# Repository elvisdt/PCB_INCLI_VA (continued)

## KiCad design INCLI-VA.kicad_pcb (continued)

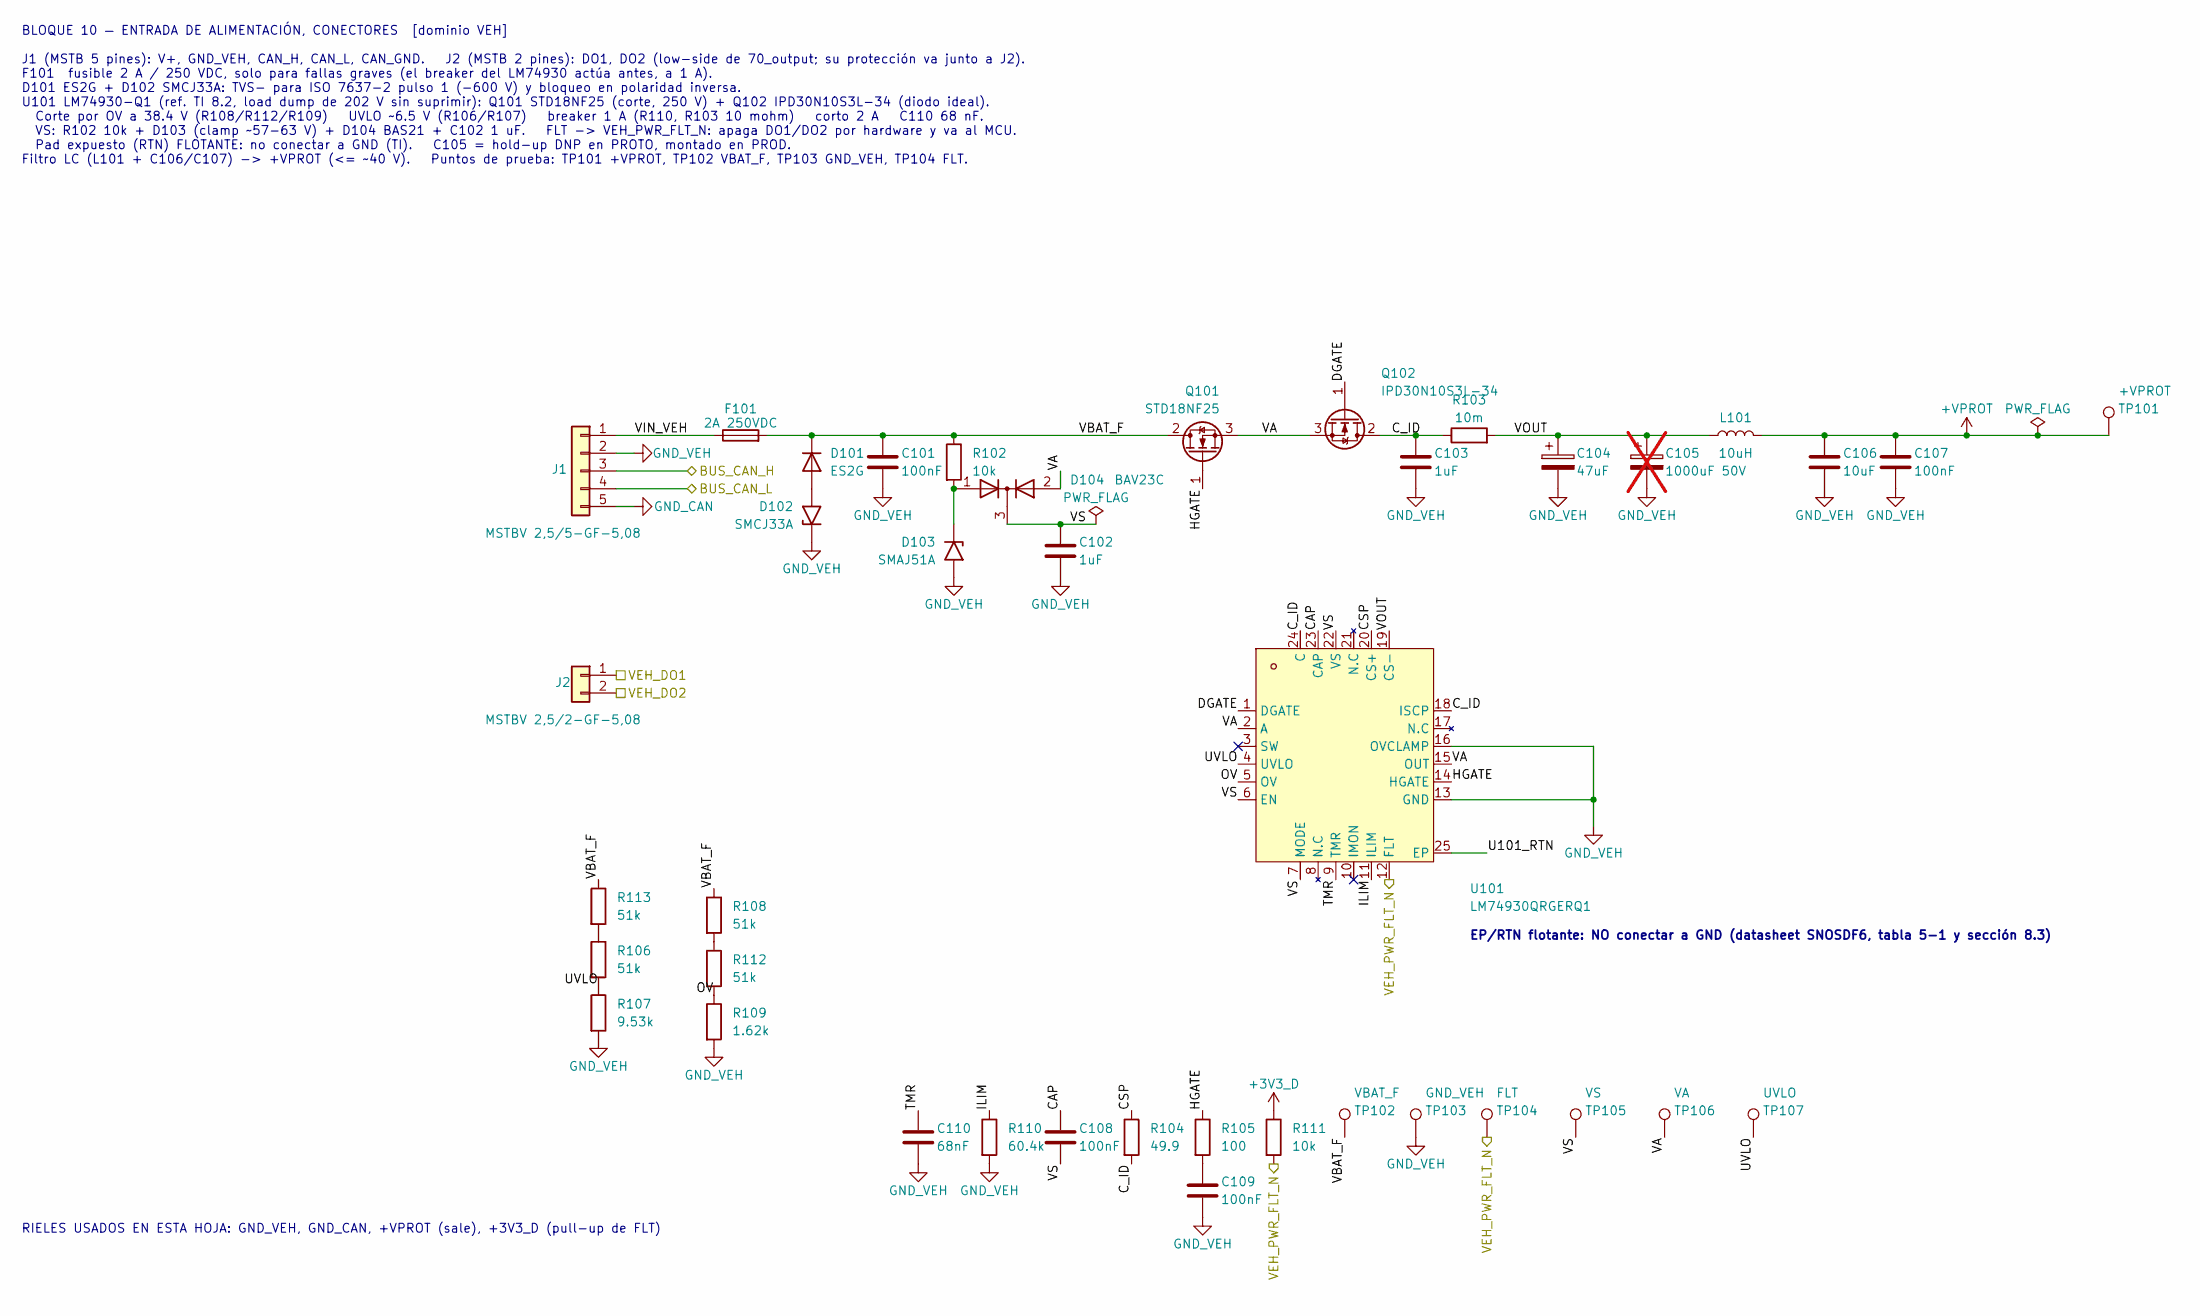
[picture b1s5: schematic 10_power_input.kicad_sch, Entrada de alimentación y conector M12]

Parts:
C101: 100nF; C_1206_3216Metric; MPN CGA5L4X7T2W104K160AA; LCSC C3887150
C102, C103: 1uF; C_1206_3216Metric; MPN CGA5L2X7R2A105K160AA; LCSC C2168321
C104: 47uF; CP_Elec_10x10; MPN EEE-HA2A470UP; LCSC C344077
C105: 1000uF 50V; CP_Elec_Panasonic_J16_VibProof; MPN EEE-FK1H102AV; LCSC C2164039; not fitted
C106: 10uF; C_1210_3225Metric; MPN GCM32ER71H106KA12L; LCSC_PROTO C138687
C107, C108, C109: 100nF; C_0603_1608Metric; MPN GCM188R72A104KA64D; LCSC C415406
C110: 68nF; C_0603_1608Metric; MPN GCM188R71H683KA57D; LCSC C380380
D101: ES2G; D_SMB; MPN ES2G-E3/52T; LCSC C2927419
D102: SMCJ33A; D_SMC; MPN SMCJ33A; LCSC C438109
D103: SMAJ51A; D_SMA; MPN SMAJ51A; LCSC C366557
D104: BAV23C; SOT-23; MPN BAV23C,215; LCSC C282370
F101: 2A 250VDC; Fuse_Bourns_SF-2410; MPN SF-2410FPA200W-2; LCSC C3159902
J1: MSTBV 2,5/5-GF-5,08; PhoenixContact_MSTBV_2,5_5-GF-5,08_1x05_P5.08mm_Vertical_Th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; MPN 1777109; LCSC C7164734
J2: MSTBV 2,5/2-GF-5,08; PhoenixContact_MSTBV_2,5_2-GF-5,08_1x02_P5.08mm_Vertical_Th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; MPN 1777073; LCSC C480552
L101: 10uH; L_Bourns_SRN6045TA; MPN SRN6045TA-100M; LCSC C2046332
Q101: STD18NF25; TO-252-2; MPN STD18NF25; LCSC C183634
Q102: IPD30N10S3L-34; TO-252-2; MPN IPD30N10S3L34ATMA1; LCSC C148263
R102: 10k; R_2512_6332Metric; MPN AC2512FK-0710KL; LCSC C469651
R103: 10m; R_1206_3216Metric; MPN ERJ-8BWFR010V; LCSC C2076185
R104: 49.9; R_0603_1608Metric; MPN AC0603FR-0749R9L; LCSC C144653
R105: 100; R_0603_1608Metric; MPN AC0603FR-07100RL; LCSC C125923
R106, R108, R112, R113: 51k; R_1206_3216Metric; MPN AC1206FR-0751KL; LCSC C144484
R107: 9.53k; R_0603_1608Metric; MPN AC0603FR-079K53L; LCSC C228113
R109: 1.62k; R_0603_1608Metric; MPN AC0603FR-071K62L; LCSC C227657
R110: 60.4k; R_0603_1608Metric; MPN AC0603FR-0760K4L; LCSC C227994
R111: 10k; R_0603_1608Metric; MPN AC0603FR-0710KL; LCSC C116677
TP101: +VPROT; TestPoint_Pad_D1.5mm
TP102: VBAT_F; TestPoint_Pad_D1.5mm
TP103: GND_VEH; TestPoint_Pad_D1.5mm
TP104: FLT; TestPoint_Pad_D1.5mm
TP105: VS; TestPoint_Pad_D1.5mm
TP106: VA; TestPoint_Pad_D1.5mm
TP107: UVLO; TestPoint_Pad_D1.5mm
U101: LM74930QRGERQ1; TI_RGE0024T_VQFN-24-1EP_4x4mm_P0.5mm_EP2.1mm_HandSolder_Iso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; MPN LM74930QRGERQ1; LCSC C22428070

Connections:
+3V3_D: R111.1; also elsewhere on the board
+VPROT: C106.1, C107.1, L101.2, TP101.1 (1_1); also elsewhere on the board
/10_power_input/CAP: C108.1, U101.23 (CAP)
/10_power_input/CSP: R104.1, U101.20 (CS+)
/10_power_input/C_ID: C103.1, Q102.2 (D), R103.1, R104.2, U101.18 (ISCP), U101.24 (C)
/10_power_input/DGATE: Q102.1 (G), U101.1 (DGATE)
/10_power_input/HGATE: Q101.1 (G), R105.1, U101.14 (HGATE)
/10_power_input/ILIM: R110.1, U101.11 (ILIM)
/10_power_input/OV: R109.1, R112.2, U101.5 (OV)
/10_power_input/TMR: C110.1, U101.9 (TMR)
/10_power_input/U101_RTN: U101.25 (EP)
/10_power_input/UVLO: R106.2, R107.1, TP107.1, U101.4 (UVLO)
/10_power_input/VA: D104.2 (NC), Q101.3 (S), Q102.3 (S), TP106.1, U101.2 (A), U101.15 (OUT)
/10_power_input/VBAT_F: C101.1, D101.1 (K), F101.2, Q101.2 (D), R102.1, R108.1, R113.1, TP102.1 (1_1)
/10_power_input/VIN_VEH: F101.1, J1.1
/10_power_input/VOUT: C104.1, C105.1, L101.1, R103.2, U101.19 (CS-)
/10_power_input/VS: C102.1, C108.2, D104.3 (K), TP105.1, U101.6 (EN), U101.7 (MODE), U101.22 (VS)
/BUS_CAN_H: J1.3; also elsewhere on the board
/BUS_CAN_L: J1.4; also elsewhere on the board
/PWR_FLT_N: R111.2, TP104.1 (1_1), U101.12 (FLT); also elsewhere on the board
/VEH_DO1: J2.1; also elsewhere on the board
/VEH_DO2: J2.2; also elsewhere on the board
GND_CAN: J1.5; also elsewhere on the board
GND_VEH: C101.2, C102.2, C103.2, C104.2, C105.2, C106.2, C107.2, C109.2, C110.2, D102.1 (A1), D103.2 (A2), J1.2, R107.2, R109.2, R110.2, TP103.1 (1_1), U101.13 (GND), U101.16 (OVCLAMP); also elsewhere on the board
unnamed: C109.1, R105.2
unnamed: D101.2 (A), D102.2 (A2)
unnamed: D103.1 (A1), D104.1 (A), R102.2
unnamed: R106.1, R113.2
unnamed: R108.2, R112.1

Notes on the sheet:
BLOQUE 10 — ENTRADA DE ALIMENTACIÓN, CONECTORES [dominio VEH] J1 (MSTB 5 pines): V+, GND_VEH, CAN_H, CAN_L, CAN_GND. J2 (MSTB 2 pines): DO1, DO2 (low-side de 70_output; su protección va junto a J2). F101 fusible 2 A / 250 VDC, solo para fallas graves (el breaker del LM74930 actúa antes, a 1 A). D10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
EP/RTN flotante: NO conectar a GND (datasheet SNOSDF6, tabla 5-1 y sección 8.3)
RIELES USADOS EN ESTA HOJA: GND_VEH, GND_CAN, +VPROT (sale), +3V3_D (pull-up de FLT)

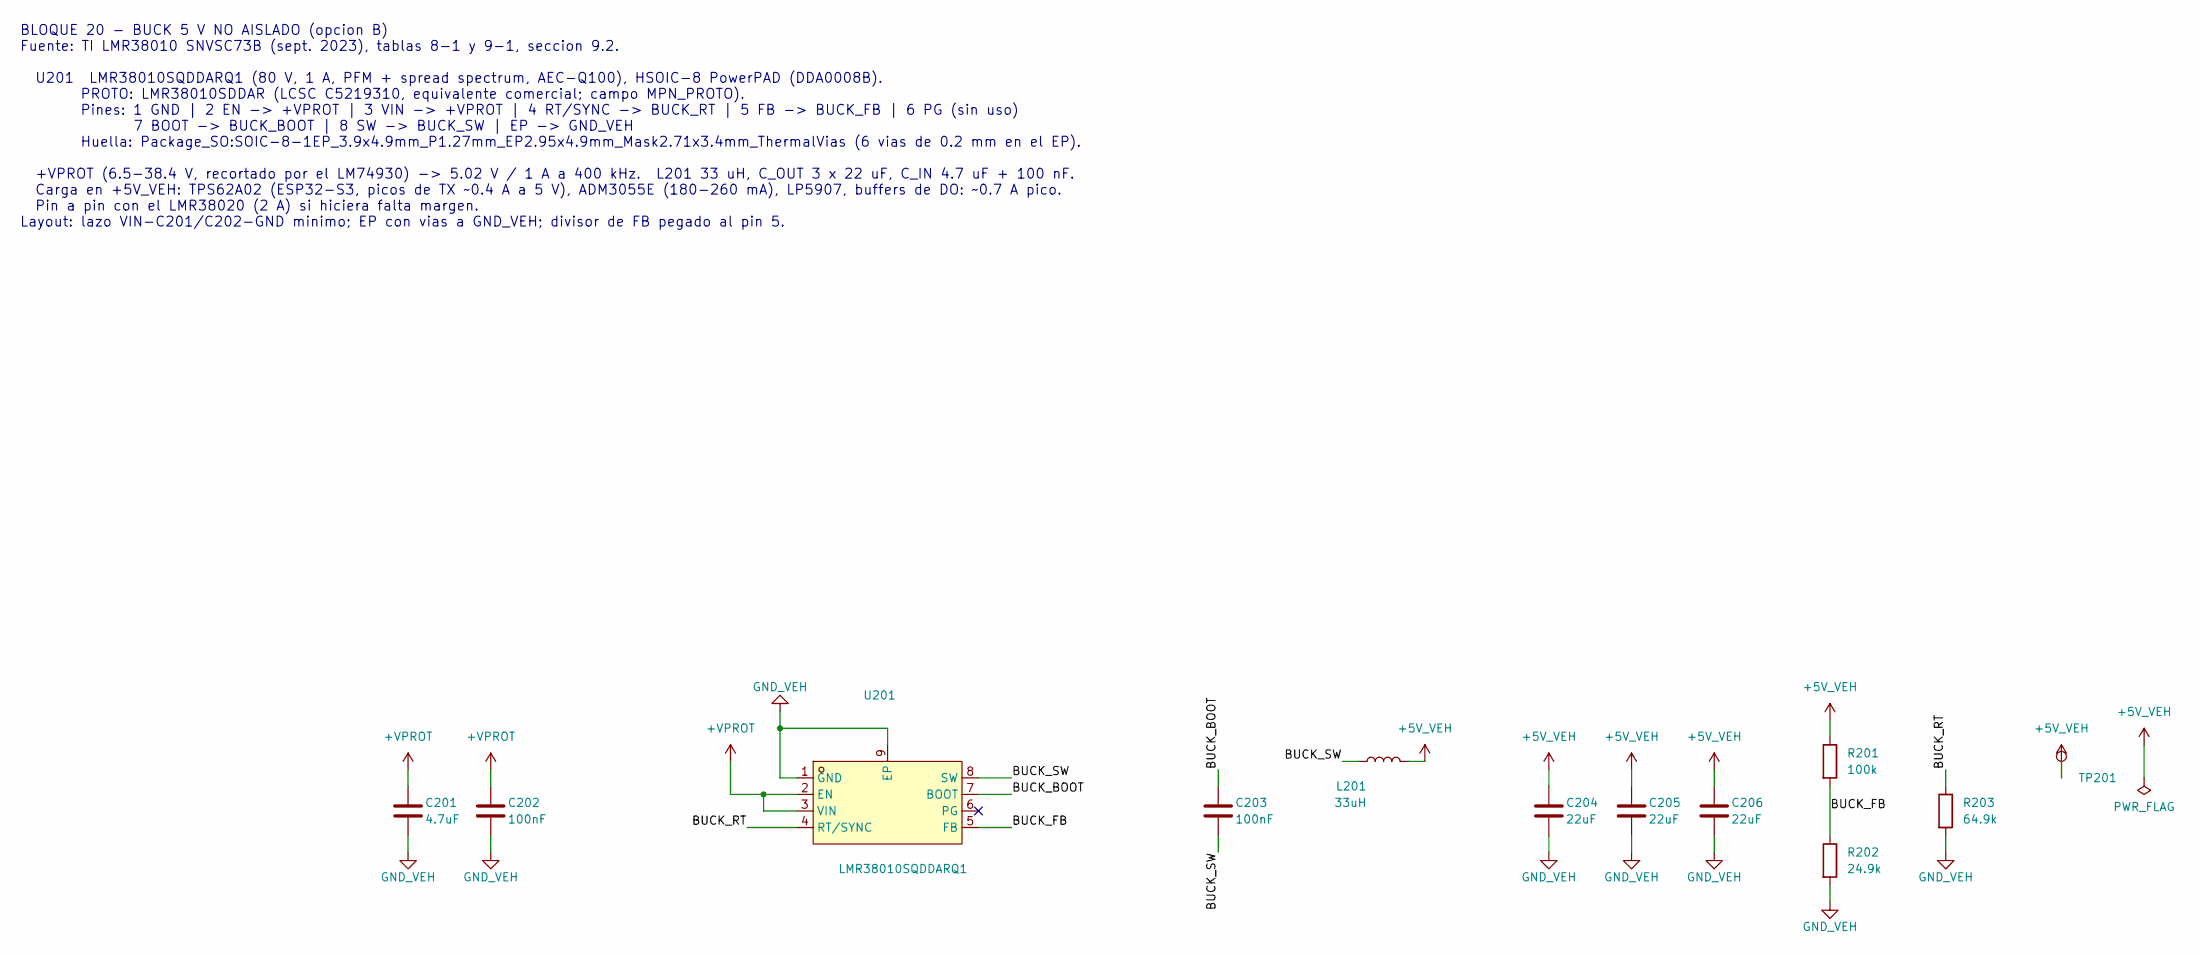
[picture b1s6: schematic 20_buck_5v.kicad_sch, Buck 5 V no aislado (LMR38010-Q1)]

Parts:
C201: 4.7uF; C_1210_3225Metric; MPN CGA6M3X7S2A475K200AB; LCSC C2168848
C202, C203: 100nF; C_0603_1608Metric; MPN GCM188R72A104KA64D; LCSC C415406
C204, C205, C206: 22uF; C_1206_3216Metric; MPN GCM31CR71A226KE02L; LCSC C126598
L201: 33uH; L_Coilcraft_XAL6060-XXX; MPN XAL6060-333MEC; LCSC C5119929
R201: 100k; R_0603_1608Metric; MPN AC0603FR-07100KL; LCSC C116674
R202: 24.9k; R_0603_1608Metric; MPN AC0603FR-0724K9L; LCSC C227732
R203: 64.9k; R_0603_1608Metric; MPN AC0603FR-0764K9L; LCSC C228007
TP201: +5V_VEH; TestPoint_Pad_D1.5mm
U201: LMR38010SQDDARQ1; SOIC-8-1EP_3.9x4.9mm_P1.27mm_EP2.95x4.9mm_Mask2.71x3.4mm_Th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; MPN LMR38010SQDDARQ1; LCSC_PROTO C5219310

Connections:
+5V_VEH: C204.1, C205.1, C206.1, L201.2, R201.1, TP201.1 (1_1); also elsewhere on the board
+VPROT: C201.1, C202.1, U201.2 (EN), U201.3 (VIN); also elsewhere on the board
/20_buck_5v/BUCK_BOOT: C203.1, U201.7 (BOOT)
/20_buck_5v/BUCK_FB: R201.2, R202.1, U201.5 (FB)
/20_buck_5v/BUCK_RT: R203.1, U201.4 (RT/SYNC)
/20_buck_5v/BUCK_SW: C203.2, L201.1, U201.8 (SW)
GND_VEH: C201.2, C202.2, C204.2, C205.2, C206.2, R202.2, R203.2, U201.1 (GND), U201.9 (EP); also elsewhere on the board

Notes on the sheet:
BLOQUE 20 - BUCK 5 V NO AISLADO (opcion B) Fuente: TI LMR38010 SNVSC73B (sept. 2023), tablas 8-1 y 9-1, seccion 9.2. U201 LMR38010SQDDARQ1 (80 V, 1 A, PFM + spread spectrum, AEC-Q100), HSOIC-8 PowerPAD (DDA0008B). PROTO: LMR38010SDDAR (LCSC C5219310, equivalente comercial; campo MPN_PROTO). Pines: 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

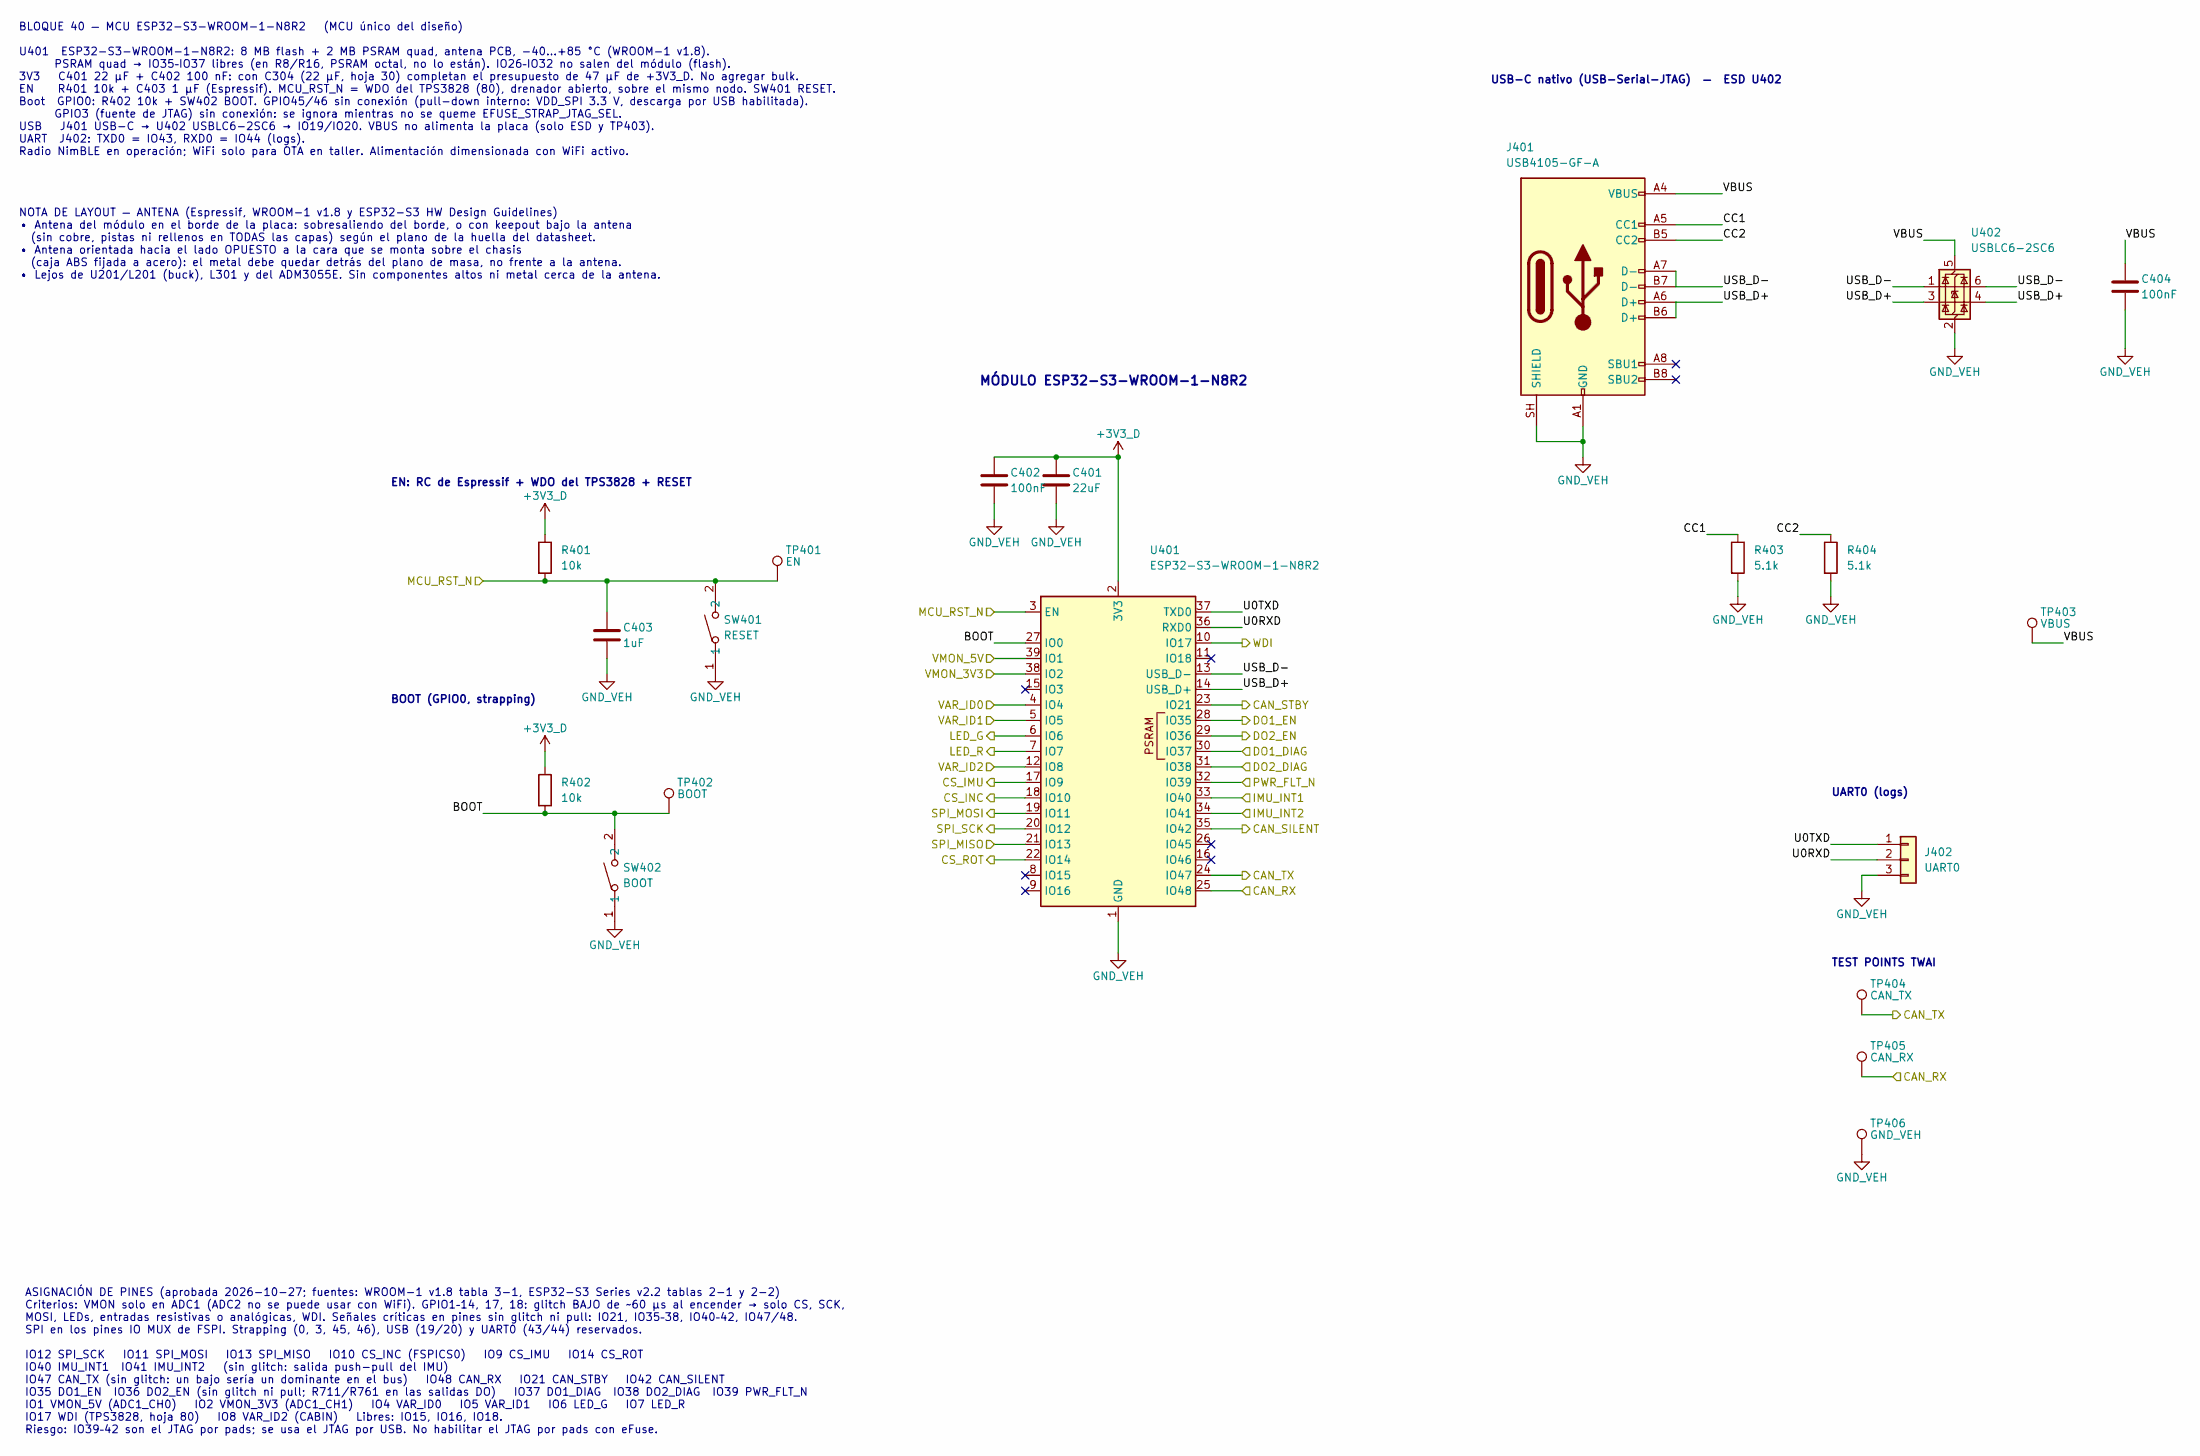
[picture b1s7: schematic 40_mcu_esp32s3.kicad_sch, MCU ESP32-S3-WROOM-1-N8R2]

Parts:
C401: 22uF; C_0805_2012Metric; MPN GRM21BZ71A226ME15L; LCSC C907991
C402, C404: 100nF; C_0603_1608Metric; MPN GCM188R72A104KA64D; LCSC C415406
C403: 1uF; C_0603_1608Metric; MPN GCM188R71C105KA64D; LCSC C161212
J401: USB4105-GF-A; USB_C_Receptacle_GCT_USB4105-xx-A_16P_TopMnt_Horizontal; MPN USB4105-GF-A; LCSC C3020560
J402: UART0; PinHeader_1x03_P2.54mm_Vertical; MPN 61300311121; LCSC C2915006
R401, R402: 10k; R_0603_1608Metric; MPN AC0603FR-0710KL; LCSC C116677
R403, R404: 5.1k; R_0603_1608Metric; MPN AC0603FR-075K1L; LCSC C125891
SW401: RESET; SW-SMD_L3.9-W3.0-P4.45; MPN TS-1088-AR02016; LCSC C720477
SW402: BOOT; SW-SMD_L3.9-W3.0-P4.45; MPN TS-1088-AR02016; LCSC C720477
TP401: EN; TestPoint_Pad_D1.5mm
TP402: BOOT; TestPoint_Pad_D1.5mm
TP403: VBUS; TestPoint_Pad_D1.5mm
TP404: CAN_TX; TestPoint_Pad_D1.5mm
TP405: CAN_RX; TestPoint_Pad_D1.5mm
TP406: GND_VEH; TestPoint_THTPad_D2.5mm_Drill1.2mm
U401: ESP32-S3-WROOM-1-N8R2; ESP32-S3-WROOM-1; MPN ESP32-S3-WROOM-1-N8R2; LCSC C2913204
U402: USBLC6-2SC6; SOT-23-6; MPN USBLC6-2SC6; LCSC C2687116

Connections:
+3V3_D: C401.1, C402.1, R401.1, R402.1, U401.2 (3V3); also elsewhere on the board
/40_mcu/BOOT: R402.2, SW402.2, TP402.1 (1_1), U401.27 (IO0)
/40_mcu/CC1: J401.A5 (CC1), R403.1
/40_mcu/CC2: J401.B5 (CC2), R404.1
/40_mcu/U0RXD: J402.2, U401.36 (RXD0)
/40_mcu/U0TXD: J402.1, U401.37 (TXD0)
/40_mcu/USB_D+: J401.A6 (D+), J401.B6 (D+), U401.14 (USB_D+), U402.3 (I/O2), U402.4 (I/O2)
/40_mcu/USB_D-: J401.A7 (D-), J401.B7 (D-), U401.13 (USB_D-), U402.1 (I/O1), U402.6 (I/O1)
/40_mcu/VBUS: C404.1, J401.A4 (VBUS), J401.A9 (VBUS), J401.B4 (VBUS), J401.B9 (VBUS), TP403.1 (1_1), U402.5 (VBUS)
/CAN_RX: TP405.1 (1_1), U401.25 (IO48); also elsewhere on the board
/CAN_SILENT: U401.35 (IO42); also elsewhere on the board
/CAN_STBY: U401.23 (IO21); also elsewhere on the board
/CAN_TX: TP404.1 (1_1), U401.24 (IO47); also elsewhere on the board
/CS_IMU: U401.17 (IO9); also elsewhere on the board
/CS_INC: U401.18 (IO10); also elsewhere on the board
/CS_ROT: U401.22 (IO14); also elsewhere on the board
/DO1_DIAG: U401.30 (IO37); also elsewhere on the board
/DO1_EN: U401.28 (IO35); also elsewhere on the board
/DO2_DIAG: U401.31 (IO38); also elsewhere on the board
/DO2_EN: U401.29 (IO36); also elsewhere on the board
/IMU_INT1: U401.33 (IO40); also elsewhere on the board
/IMU_INT2: U401.34 (IO41); also elsewhere on the board
/LED_G: U401.6 (IO6); also elsewhere on the board
/LED_R: U401.7 (IO7); also elsewhere on the board
/MCU_RST_N: C403.1, R401.2, SW401.2, TP401.1 (1_1), U401.3 (EN); also elsewhere on the board
/PWR_FLT_N: U401.32 (IO39); also elsewhere on the board
/SPI_MISO: U401.21 (IO13); also elsewhere on the board
/SPI_MOSI: U401.19 (IO11); also elsewhere on the board
/SPI_SCK: U401.20 (IO12); also elsewhere on the board
/VAR_ID0: U401.4 (IO4); also elsewhere on the board
/VAR_ID1: U401.5 (IO5); also elsewhere on the board
/VAR_ID2: U401.12 (IO8); also elsewhere on the board
/VMON_3V3: U401.38 (IO2); also elsewhere on the board
/VMON_5V: U401.39 (IO1); also elsewhere on the board
/WDI: U401.10 (IO17); also elsewhere on the board
GND_VEH: C401.2, C402.2, C403.2, C404.2, J401.A1 (GND), J401.A12 (GND), J401.B1 (GND), J401.B12 (GND), J401.SH (SHIELD), J402.3, R403.2, R404.2, SW401.1, SW402.1, TP406.1, U401.1 (GND), U401.40 (GND), U401.41 (GND), U402.2 (GND); also elsewhere on the board

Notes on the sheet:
UART0 (logs)
USB-C nativo (USB-Serial-JTAG) — ESD U402
ASIGNACIÓN DE PINES (aprobada 2026-10-27; fuentes: WROOM-1 v1.8 tabla 3-1, ESP32-S3 Series v2.2 tablas 2-1 y 2-2) Criterios: VMON solo en ADC1 (ADC2 no se puede usar con WiFi). GPIO1–14, 17, 18: glitch BAJO de ~60 µs al encender → solo CS, SCK, MOSI, LEDs, entradas resistivas o analógicas, WDI. Señ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
TEST POINTS TWAI
NOTA DE LAYOUT — ANTENA (Espressif, WROOM-1 v1.8 y ESP32-S3 HW Design Guidelines) • Antena del módulo en el borde de la placa: sobresaliendo del borde, o con keepout bajo la antena (sin cobre, pistas ni rellenos en TODAS las capas) según el plano de la huella del datasheet. • Antena orientada hacia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
EN: RC de Espressif + WDO del TPS3828 + RESET
BLOQUE 40 — MCU ESP32-S3-WROOM-1-N8R2 (MCU único del diseño) U401 ESP32-S3-WROOM-1-N8R2: 8 MB flash + 2 MB PSRAM quad, antena PCB, −40…+85 °C (WROOM-1 v1.8). PSRAM quad → IO35–IO37 libres (en R8/R16, PSRAM octal, no lo están). IO26–IO32 no salen del módulo (flash). 3V3 C401 22 µF + C402 100 nF: con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
BOOT (GPIO0, strapping)
MÓDULO ESP32-S3-WROOM-1-N8R2

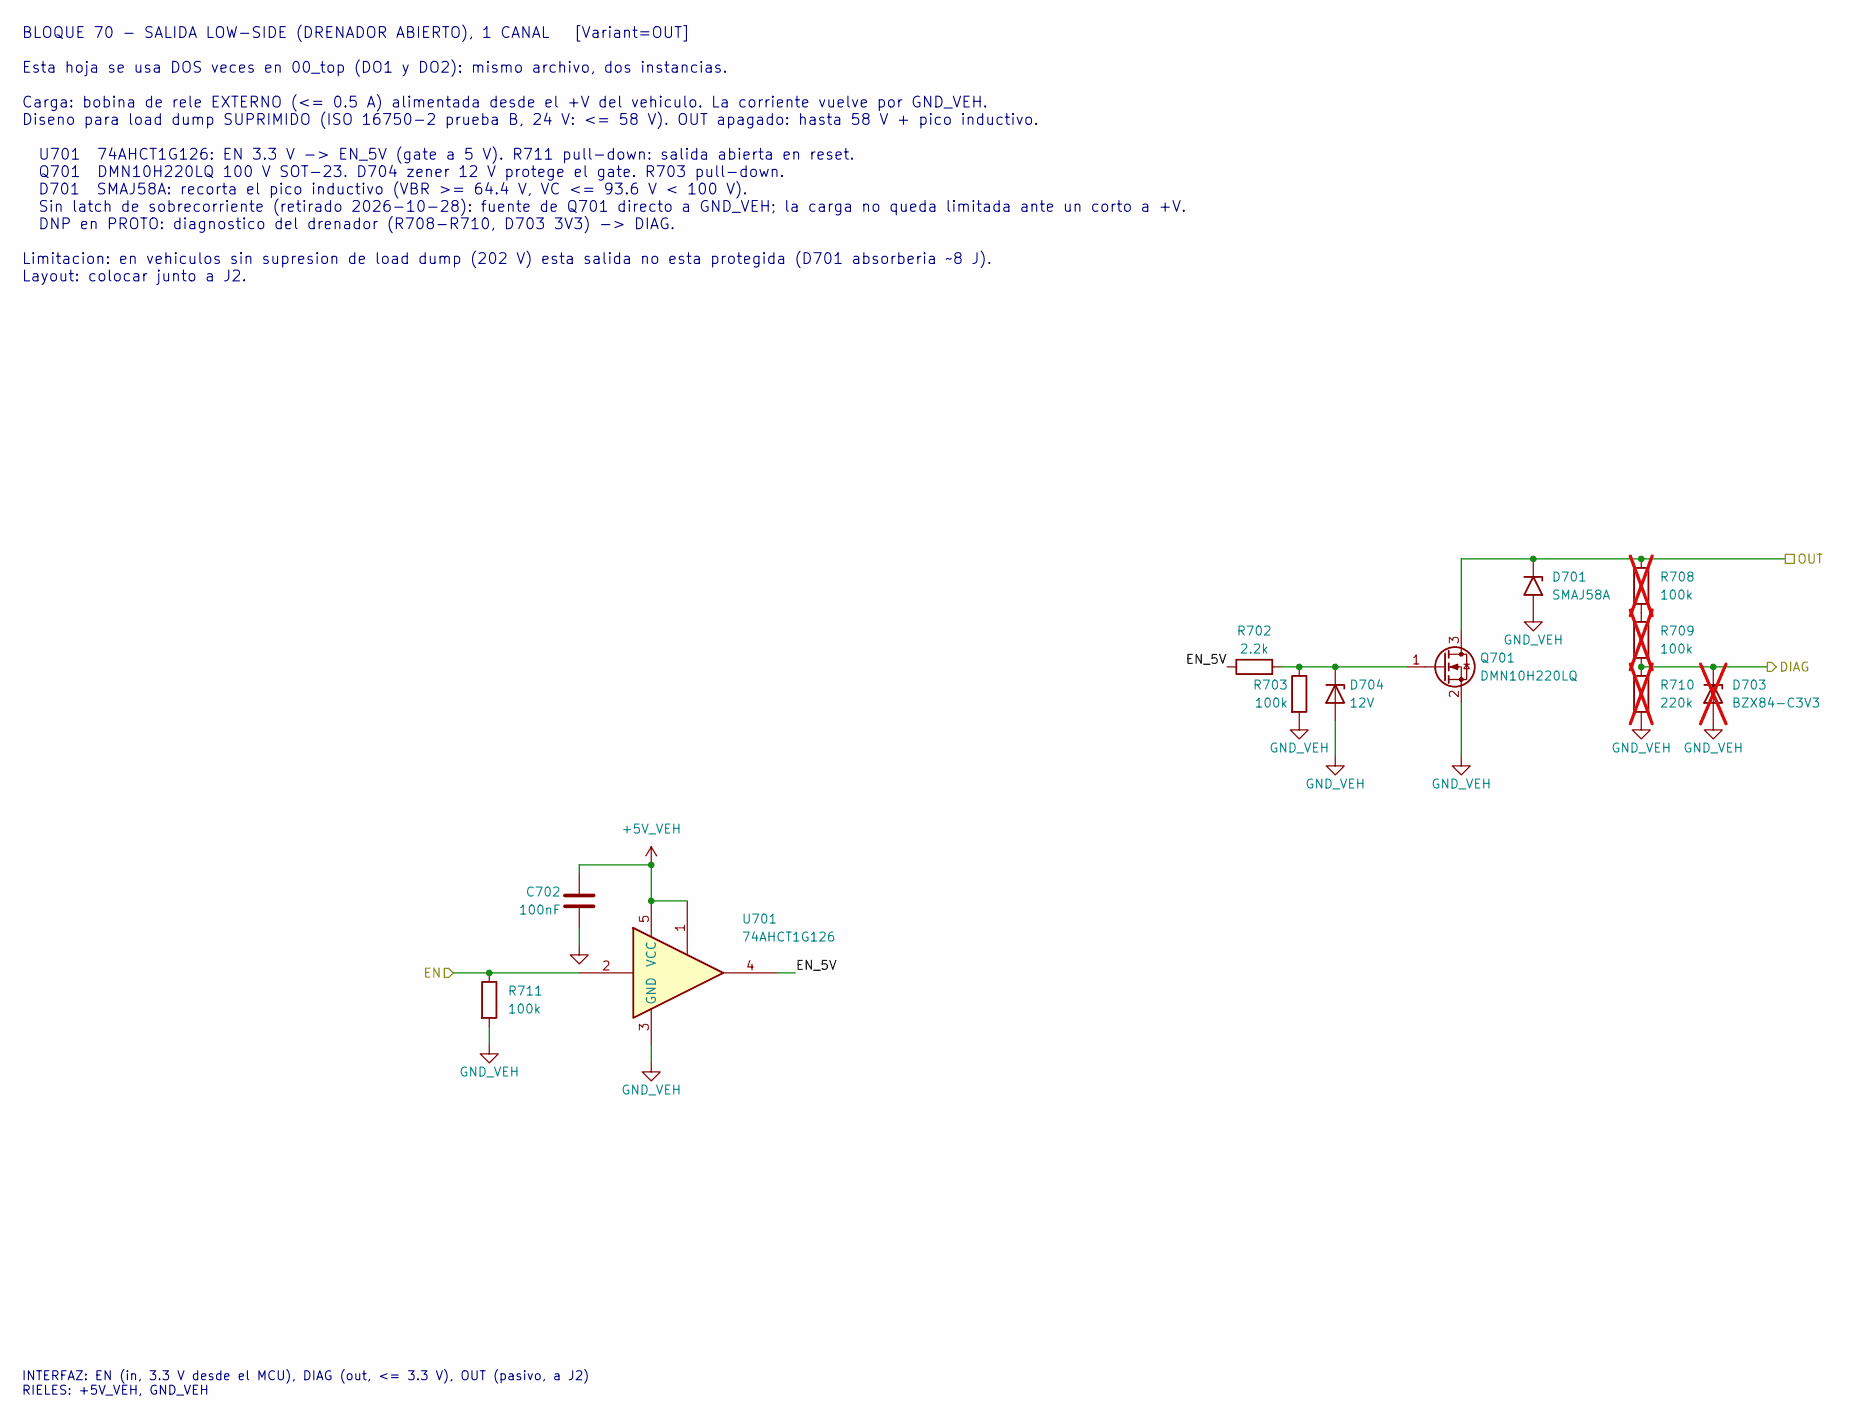
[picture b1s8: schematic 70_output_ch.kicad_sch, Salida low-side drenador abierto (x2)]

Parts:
C702: 100nF; C_0603_1608Metric; MPN GCM188R72A104KA64D; LCSC C415406
D701: SMAJ58A; D_SMA; MPN SMAJ58A; LCSC C123816
D703: BZX84-C3V3; SOT-23; MPN BZX84-C3V3,215; LCSC C85087; not fitted
D704: 12V; D_SOD-123; MPN MMSZ5242B-7-F; LCSC C500776
Q701: DMN10H220LQ; SOT-23; MPN DMN10H220LQ-7; LCSC C5260572
R702: 2.2k; R_0603_1608Metric; MPN AC0603FR-072K2L; LCSC C125931
R703, R711: 100k; R_0603_1608Metric; MPN AC0603FR-07100KL; LCSC C116674
R708, R709: 100k; R_1206_3216Metric; MPN AC1206FR-07100KL; LCSC C144522; not fitted
R710: 220k; R_0603_1608Metric; MPN AC0603FR-07220KL; LCSC C144681; not fitted
U701: 74AHCT1G126; SOT-23-5; MPN SN74AHCT1G126QDBVRQ1; LCSC_PROTO C163712

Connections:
+5V_VEH: C702.1, U701.1, U701.5 (VCC); also elsewhere on the board
/70_output_DO1/EN_5V: R702.1, U701.4
/DO1_DIAG: D703.3 (K), R709.2, R710.1; also elsewhere on the board
/DO1_EN: R711.1, U701.2; also elsewhere on the board
/VEH_DO1: D701.1 (A1), Q701.3 (D), R708.1; also elsewhere on the board
GND_VEH: C702.2, D701.2 (A2), D703.1 (A), D704.2 (A), Q701.2 (S), R703.2, R710.2, R711.2, U701.3 (GND); also elsewhere on the board
unnamed: D704.1 (K), Q701.1 (G), R702.2, R703.1
unnamed: R708.2, R709.1

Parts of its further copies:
C752: 100nF; C_0603_1608Metric; MPN GCM188R72A104KA64D; LCSC C415406
D751: SMAJ58A; D_SMA; MPN SMAJ58A; LCSC C123816
D753: BZX84-C3V3; SOT-23; MPN BZX84-C3V3,215; LCSC C85087; not fitted
D754: 12V; D_SOD-123; MPN MMSZ5242B-7-F; LCSC C500776
Q751: DMN10H220LQ; SOT-23; MPN DMN10H220LQ-7; LCSC C5260572
R752: 2.2k; R_0603_1608Metric; MPN AC0603FR-072K2L; LCSC C125931
R753, R761: 100k; R_0603_1608Metric; MPN AC0603FR-07100KL; LCSC C116674
R758, R759: 100k; R_1206_3216Metric; MPN AC1206FR-07100KL; LCSC C144522; not fitted
R760: 220k; R_0603_1608Metric; MPN AC0603FR-07220KL; LCSC C144681; not fitted
U751: 74AHCT1G126; SOT-23-5; MPN SN74AHCT1G126QDBVRQ1; LCSC_PROTO C163712

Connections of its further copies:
+5V_VEH: C752.1, U751.1, U751.5 (VCC); also elsewhere on the board
/70_output_DO2/EN_5V: R752.1, U751.4
/DO2_DIAG: D753.3 (K), R759.2, R760.1; also elsewhere on the board
/DO2_EN: R761.1, U751.2; also elsewhere on the board
/VEH_DO2: D751.1 (A1), Q751.3 (D), R758.1; also elsewhere on the board
GND_VEH: C752.2, D751.2 (A2), D753.1 (A), D754.2 (A), Q751.2 (S), R753.2, R760.2, R761.2, U751.3 (GND); also elsewhere on the board
unnamed: D754.1 (K), Q751.1 (G), R752.2, R753.1
unnamed: R758.2, R759.1

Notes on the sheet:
INTERFAZ: EN (in, 3.3 V desde el MCU), DIAG (out, <= 3.3 V), OUT (pasivo, a J2) RIELES: +5V_VEH, GND_VEH
BLOQUE 70 - SALIDA LOW-SIDE (DRENADOR ABIERTO), 1 CANAL [Variant=OUT] Esta hoja se usa DOS veces en 00_top (DO1 y DO2): mismo archivo, dos instancias. Carga: bobina de rele EXTERNO (<= 0.5 A) alimentada desde el +V del vehiculo. La corriente vuelve por GND_VEH. Diseno para load dump SUPRIMIDO (ISO 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

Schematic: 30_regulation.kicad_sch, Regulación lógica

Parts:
C301: 10uF; C_0805_2012Metric; MPN GCM21BR71A106KE22L; LCSC C126586
C302, C309, C310: 100nF; C_0603_1608Metric; MPN GCM188R72A104KA64D; LCSC C415406
C303: 10pF; C_0603_1608Metric; MPN GCM1885C1H100JA16D; LCSC C126542
C304: 22uF; C_0805_2012Metric; MPN GRM21BZ71A226ME15L; LCSC C907991
C306, C307: 1uF; C_0603_1608Metric; MPN GCM188R71C105KA64D; LCSC C161212
FB301: 220R@100MHz; L_0603_1608Metric; MPN BLM18PG221SN1D; LCSC C80165
L301: 1uH; L_Coilcraft_XAL4020_HandSolder; MPN XAL4020-102MEC; LCSC C4555951
R301, R302, R304, R305, R307, R308: 100k; R_0603_1608Metric; MPN AC0603FR-07100KL; LCSC C116674
R303: 453k; R_0603_1608Metric; MPN AC0603FR-07453KL; LCSC C227908
R306: 49.9k; R_0603_1608Metric; MPN AC0603FR-0749K9L; LCSC C144654
TP301: +5V_VEH; TestPoint_Pad_D1.5mm
TP302: +3V3_D; TestPoint_Pad_D1.5mm
TP303: +3V3_A; TestPoint_Pad_D1.5mm
TP304: GND_VEH; TestPoint_Pad_D1.5mm
TP305: PG_3V3D; TestPoint_Pad_D1.5mm
U301: TPS62A02QDRLRQ1; SOT-563; MPN TPS62A02QDRLRQ1; LCSC C49259289
U302: LP5907QMFX-3.3Q1; SOT-23-5; MPN LP5907QMFX-3.3Q1; LCSC C130005

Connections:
+3V3_A: C307.1, TP303.1 (1_1), U302.5 (OUT); also elsewhere on the board
+3V3_D: C303.1, C304.1, L301.2, R302.1, R303.1, R307.1, TP302.1 (1_1); also elsewhere on the board
+5V_VEH: C301.1, C302.1, FB301.1, R301.1, R305.1, TP301.1 (1_1), U301.3 (VIN); also elsewhere on the board
/30_regulation/PG_3V3D: R302.2, TP305.1 (1_1), U301.6 (PG)
/VMON_3V3: C310.1, R307.2, R308.1; also elsewhere on the board
/VMON_5V: C309.1, R305.2, R306.1; also elsewhere on the board
GND_VEH: C301.2, C302.2, C304.2, C306.2, C307.2, C309.2, C310.2, R304.2, R306.2, R308.2, TP304.1 (1_1), U301.1 (GND), U302.2 (GND); also elsewhere on the board
unnamed: R301.2, U301.4 (EN)
unnamed: C303.2, R303.2, R304.1, U301.5 (FB)
unnamed: L301.1, U301.2 (SW)
unnamed: C306.1, FB301.2, U302.1 (IN), U302.3 (EN)

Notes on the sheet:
MONITOREO → ADC1 del ESP32-S3
LDO +5V_VEH → +3V3_A (sensores)
BUCK +5V_VEH → +3V3_D
BLOQUE 30 — REGULACIÓN Entrada: +5V_VEH (buck LMR38010, hoja 20_buck_5v). Salidas: +3V3_D (buck U301) y +3V3_A (LDO U302). Interfaz: VMON_5V, VMON_3V3 (out, a ADC1). U301 TPS62A02QDRLRQ1, 2.2 MHz, PSM. L301 1 µH XAL4020-102MEC (Isat 8.7 A). ΔIL = 3.3·(1−3.3/5) / (1 µH·2.2 MHz) = 0.51 A pp; pico a 0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
